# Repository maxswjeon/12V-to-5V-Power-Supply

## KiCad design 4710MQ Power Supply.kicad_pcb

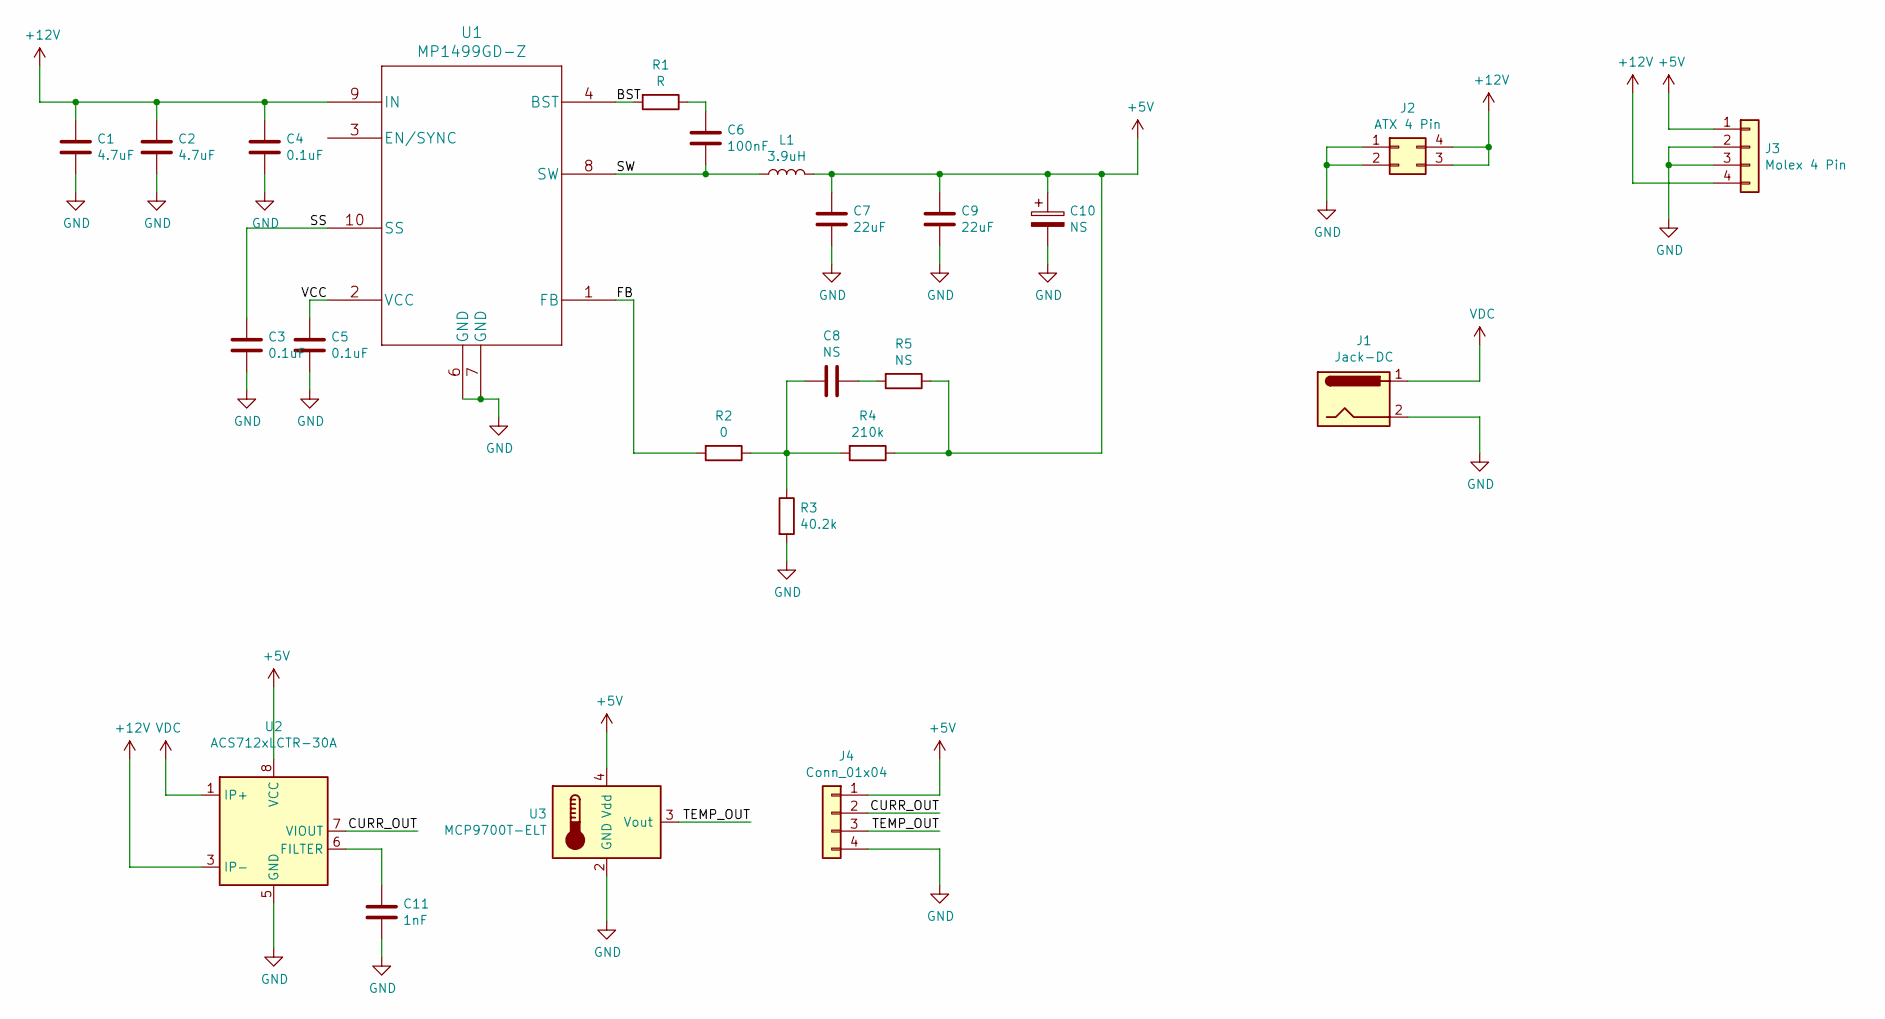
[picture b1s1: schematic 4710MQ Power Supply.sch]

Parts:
C1, C2: 4.7uF; C_1206_3216Metric_Pad1.33x1.80mm_HandSolder
C3, C4, C5: 0.1uF; C_0805_2012Metric_Pad1.18x1.45mm_HandSolder
C6: 100nF; C_0805_2012Metric_Pad1.18x1.45mm_HandSolder
C7, C9: 22uF; C_1206_3216Metric_Pad1.33x1.80mm_HandSolder
C8, C10: NS; C_0805_2012Metric_Pad1.18x1.45mm_HandSolder
C11: 1nF; C_0805_2012Metric_Pad1.18x1.45mm_HandSolder
J1: Jack-DC; DC015
J2: ATX 4 Pin; Molex_Mini-Fit_Jr_5566-04A_2x02_P4.20mm_Vertical
J3: Molex 4 Pin; PhoenixContact_MCV_1,5_4-G-5.08_1x04_P5.08mm_Vertical
J4: Conn_01x04; PinSocket_1x04_P2.54mm_Vertical
L1: 3.9uH; L_TDK_SLF12575
R1: R; R_0603_1608Metric_Pad0.98x0.95mm_HandSolder
R2: 0; R_0603_1608Metric_Pad0.98x0.95mm_HandSolder
R3: 40.2k; R_0603_1608Metric_Pad0.98x0.95mm_HandSolder
R4: 210k; R_0603_1608Metric_Pad0.98x0.95mm_HandSolder
R5: NS; R_0603_1608Metric_Pad0.98x0.95mm_HandSolder
U1: MP1499GD-Z
U2: ACS712xLCTR-30A; SOIC-8_3.9x4.9mm_P1.27mm
U3: MCP9700T-ELT; SOT-353_SC-70-5

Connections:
+5V: C7.1, C9.1, C10.1, J3.1, J4.1, L1.2, R4.1, R5.1, U2.8 (VCC), U3.4 (Vdd)
+12V: C1.1, C2.1, C4.1, J2.3, J2.4, J3.4, U1.9 (IN), U2.3 (IP-), U2.4 (IP-)
/BST: R1.2, U1.4 (BST)
/CURR_OUT: J4.2, U2.7 (VIOUT)
/FB: R2.2, U1.1 (FB)
/SS: C3.1, U1.10 (SS)
/SW: C6.2, L1.1, U1.8 (SW)
/TEMP_OUT: J4.3, U3.3 (Vout)
/VCC: C5.1, U1.2 (VCC)
GND: C1.2, C2.2, C3.2, C4.2, C5.2, C7.2, C9.2, C10.2, C11.2, J1.2, J2.1, J2.2, J3.2, J3.3, J4.4, R3.2, U1.6 (GND), U1.7 (GND), U2.5 (GND), U3.2 (GND)
unnamed: C6.1, R1.1
unnamed: C8.1, R5.2
unnamed: C8.2, R2.1, R3.1, R4.2
unnamed: C11.1, U2.6 (FILTER)
VDC: J1.1, U2.1 (IP+), U2.2 (IP+)

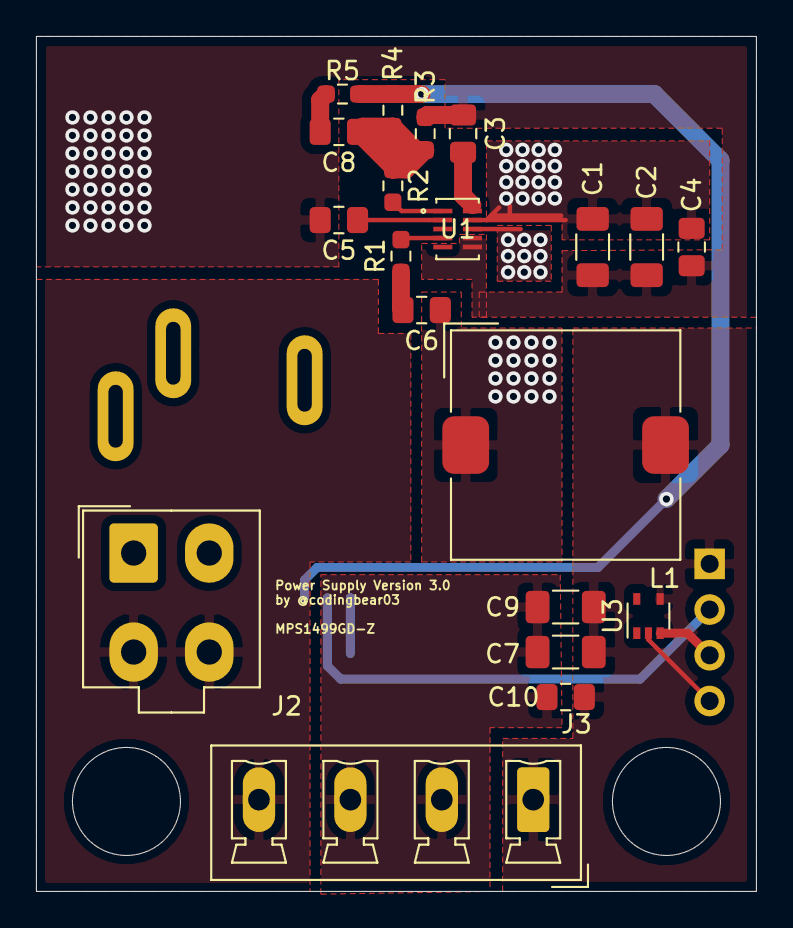
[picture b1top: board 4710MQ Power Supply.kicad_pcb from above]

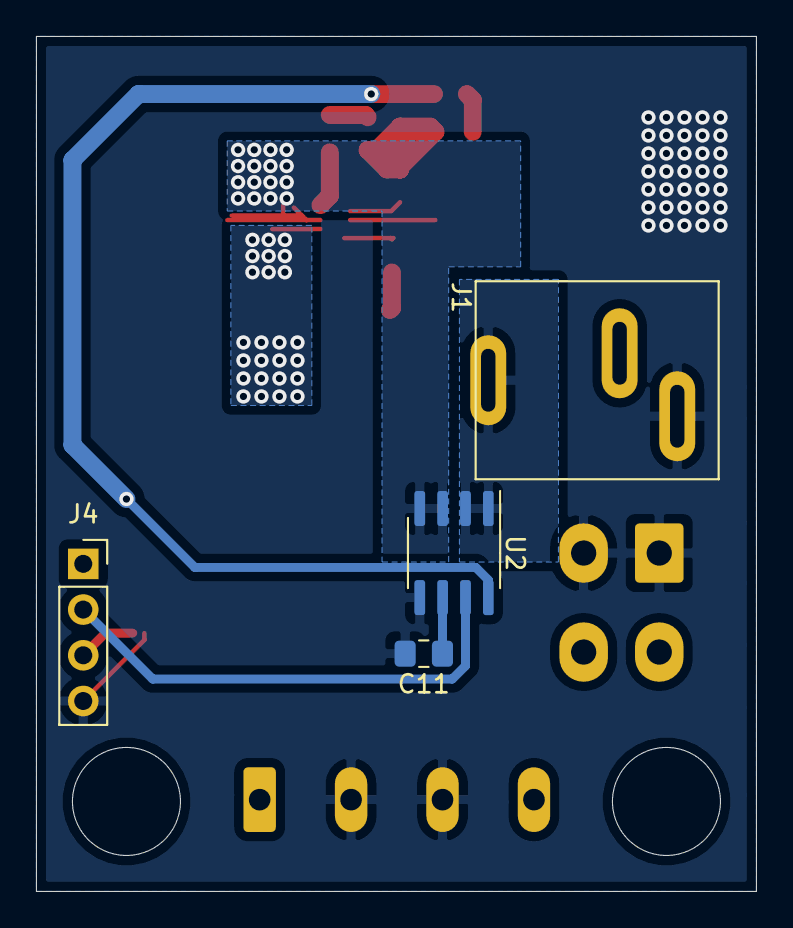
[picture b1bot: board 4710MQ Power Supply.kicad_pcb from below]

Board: 2 copper layers, 40.0 x 47.5 mm, 24 parts (4 on the bottom side), 15 nets.

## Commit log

2021-07-15 Version 1.0 Finsished
    - Basic DC to DC Buck Converter with MP1499GD-P (Peak 5A)
2021-07-15 Version 1.1
    - Add DC-015 (Vertical DC Jack)
    - Removed Jumpers (Innerside - +12V / Outside - GND fixed)
2021-07-15 [Not Completed] Version 1.2
    - 3.3V LDO
    - Current Sensor up to 30A
    - UART to USB (CH340G)
    - ADC 12bit
2021-07-16 Version 2.0
    - Size Changed
2021-07-16 Version 3.0
    - Added Current Sensor
    - Added Thermometer IC
    - Added 2.54 pitch 4pin output
